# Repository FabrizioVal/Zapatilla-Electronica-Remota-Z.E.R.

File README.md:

# Este proyecto se a redirigido [aquí!](https://github.com/RodrigoSturm14/Zapatilla-Electronica-Remota-Z.E.R-)

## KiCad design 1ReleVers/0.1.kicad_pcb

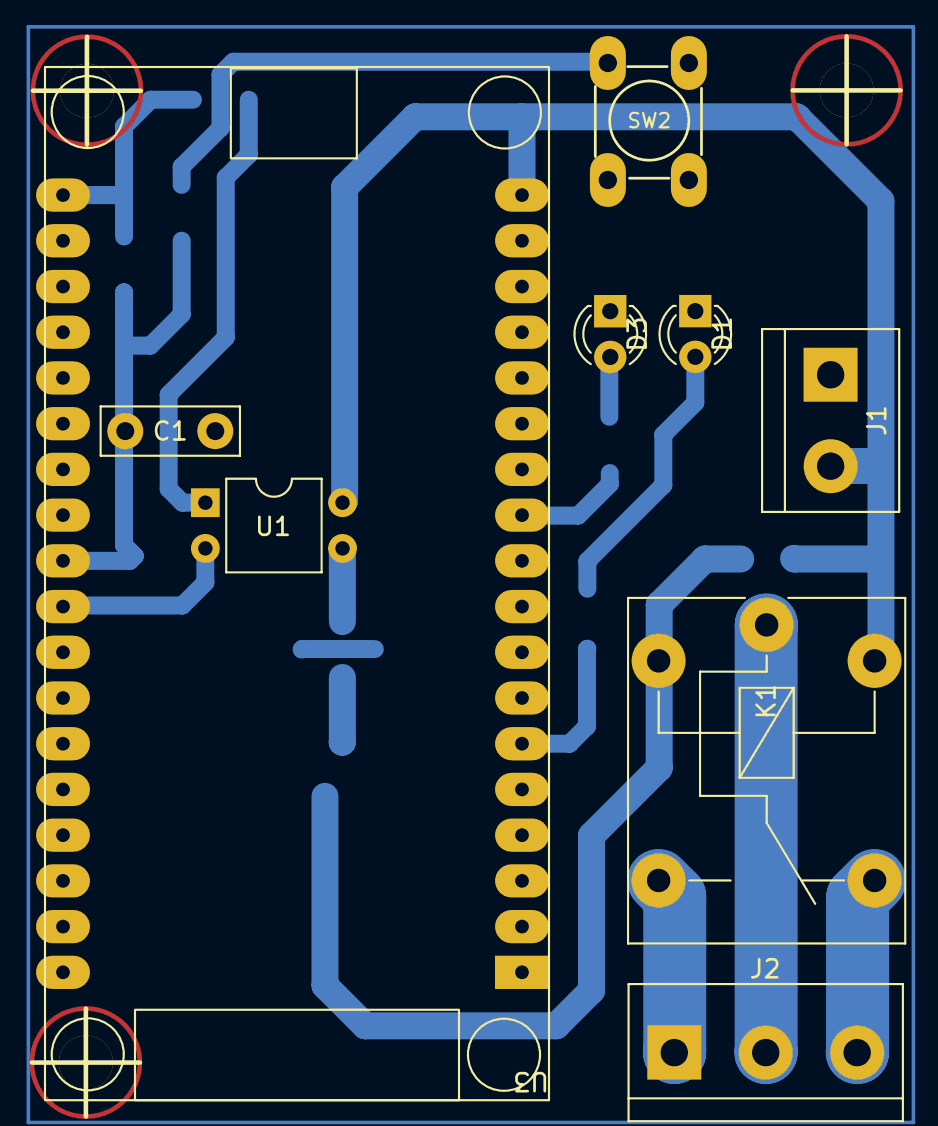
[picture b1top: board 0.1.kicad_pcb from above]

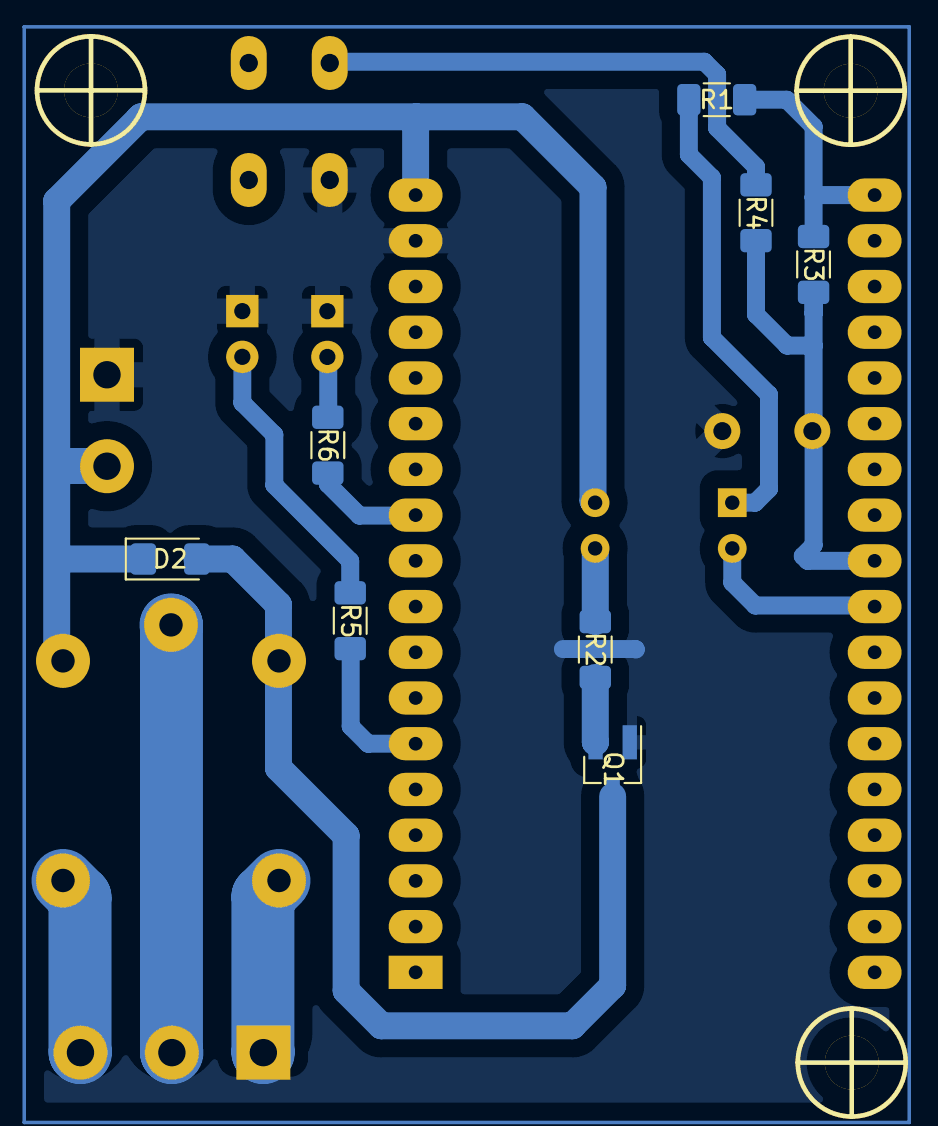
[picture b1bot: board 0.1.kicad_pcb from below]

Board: 2 copper layers, 20 parts (8 on the bottom side), 17 nets.

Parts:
C1: C; C_Disc_D7.5mm_W2.5mm_P5.00mm
D1, D3: LED; LED_D3.0mm
D2: D_Shockley; D_1206_3216Metric_Pad1.42x1.75mm_HandSolder
J1: Entrada 5v; TerminalBlock_bornier-2_P5.08mm
J2: Relay1; TerminalBlock_bornier-3_P5.08mm
K1: G5V-1; Relay_SPDT_Finder_36.11
Q1: S8050; SOT-23_Handsoldering
R1, R2: 1k; R_1206_3216Metric_Pad1.30x1.75mm_HandSolder
R3: 4,7k; R_1206_3216Metric_Pad1.30x1.75mm_HandSolder
R4, R5, R6: R; R_1206_3216Metric_Pad1.30x1.75mm_HandSolder
SW2: SW_Push; PUSH_SWITCH_THT
U1: PC817; DIP-4_W7.62mm
U3: ESP32_DevKit_V1_DOIT; ESP32_Devkit_V1_36pin
hole_3mm, hole_3mm#2, hole_3mm#3: VAL**; hole_3mm

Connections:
+3V3: R1.1, R3.1, U3.19 (3V3)
+5V: D2.1 (K), J1.2, K1.2, U1.4, U3.18 (VIN)
/BT_Config: C1.1, R3.2, R4.2, U3.27 (RX2)
/COM1: J2.2, K1.5
/IN1: U1.2, U3.28 (TX2)
/LED_ConfigBT: R5.1, U3.6 (IO32)
/LED_ConfigWIFI: R6.1, U3.11 (IO14)
/NC1: J2.3, K1.1
/NO1: J2.1, K1.10
GND: C1.2, D1.1 (K), D3.1 (K), J1.1, Q1.1 (E), SW2.2, U3.17 (GND)
unnamed: D1.2 (A), R5.2
unnamed: D2.2 (A), K1.9, Q1.3 (C)
unnamed: D3.2 (A), R6.2
unnamed: Q1.2 (B), R2.2
unnamed: R1.2, U1.1
unnamed: R2.1, U1.3
unnamed: R4.1, SW2.1

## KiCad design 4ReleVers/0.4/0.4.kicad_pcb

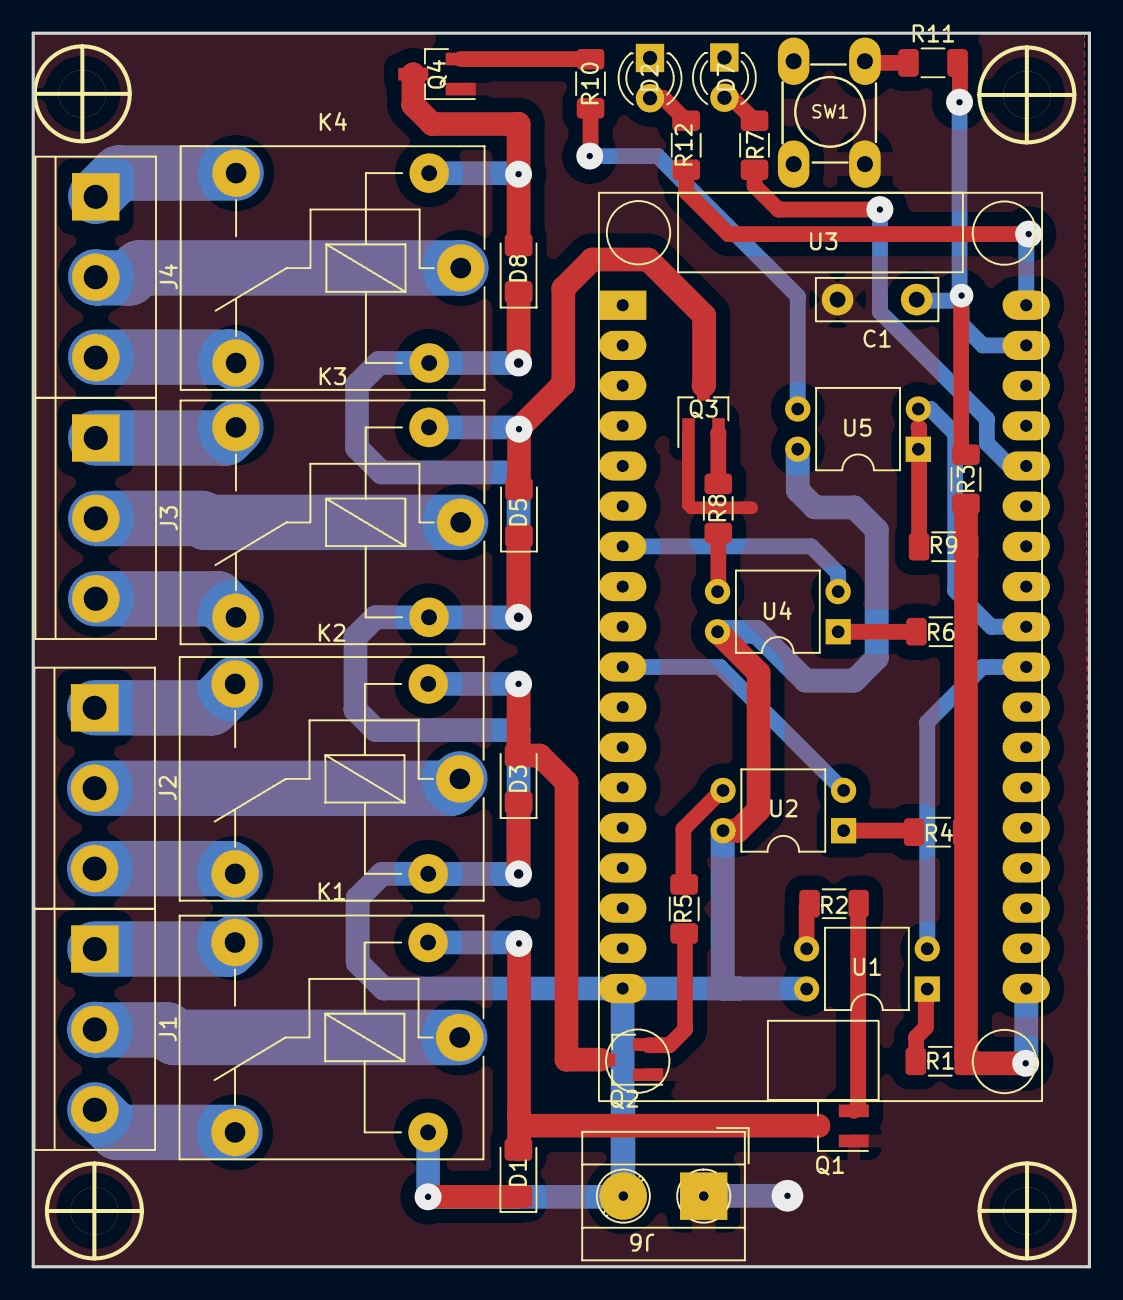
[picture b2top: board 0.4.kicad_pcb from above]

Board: 2 copper layers, 66.7 x 78.0 mm, 42 parts (0 on the bottom side), 41 nets.

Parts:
C1: C; C_Disc_D7.5mm_W2.5mm_P5.00mm
D1, D3, D5, D8: D_Shockley; D_1206_3216Metric_Pad1.42x1.75mm_HandSolder
D2, D7: LED; LED_D3.0mm
J1: Relay1; TerminalBlock_bornier-3_P5.08mm
J2: Relay2; TerminalBlock_bornier-3_P5.08mm
J3: Relay3; TerminalBlock_bornier-3_P5.08mm
J4: Relay4; TerminalBlock_bornier-3_P5.08mm
J6: Entrada 5V; TerminalBlock_1x02_P5.08mm_Horizontal_Personal
K1, K2, K3, K4: G5V-1; Relay_SPDT_Finder_36.11
Q1, Q2, Q3, Q4: S8050; SOT-23_Handsoldering
R1, R2, R4, R5, R6, R8, R9, R10: 1k; R_1206_3216Metric_Pad1.30x1.75mm_HandSolder
R3: 4,7k; R_1206_3216Metric_Pad1.30x1.75mm_HandSolder
R7, R11, R12: R; R_1206_3216Metric_Pad1.30x1.75mm_HandSolder
SW1: SW_Push; PUSH_SWITCH_THT
U1, U2, U4, U5: PC817; DIP-4_W7.62mm
U3: ESP32_DevKit_V1_DOIT; ESP32_Devkit_V1_36pin
hole_3mm, hole_3mm#2, hole_3mm#3, hole_3mm#4: VAL**; hole_3mm

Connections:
+3V3: R1.1, R3.1, R4.1, R6.1, R9.1, U3.19 (3V3)
+5V: D1.1 (K), D3.1 (K), D5.1 (K), D8.1 (K), J6.2, K1.2, K2.2, K3.2, K4.2, U1.4, U2.4, U3.18 (VIN), U4.4, U5.4
/BT_Config: C1.1, R3.2, R11.2, U3.35 (IO22)
/COM1: J1.2, K1.5
/COM2: J2.2, K2.5
/COM3: J3.2, K3.5
/COM4: J4.2, K4.5
/IN1: U1.2, U3.27 (RX2)
/IN2: U2.2, U3.10 (IO27)
/IN3: U3.7 (IO33), U4.2
/IN4: U3.28 (TX2), U5.2
/LED_ConfigBT: R12.1, U3.36 (IO23)
/LED_ConfigWIFI: R7.1, U3.32 (IO21)
/NC1: J1.3, K1.1
/NC2: J2.3, K2.1
/NC3: J3.3, K3.1
/NC4: J4.3, K4.1
/NO1: J1.1, K1.10
/NO2: J2.1, K2.10
/NO3: J3.1, K3.10
/NO4: J4.1, K4.10
GND: C1.2, D2.1 (K), D7.1 (K), J6.1, Q1.1 (E), Q2.1 (E), Q3.1 (E), Q4.1 (E), SW1.2, U3.17 (GND)
unnamed: D1.2 (A), K1.9, Q1.3 (C)
unnamed: D2.2 (A), R12.2
unnamed: D3.2 (A), K2.9, Q2.3 (C)
unnamed: D5.2 (A), K3.9, Q3.3 (C)
unnamed: D7.2 (A), R7.2
unnamed: D8.2 (A), K4.9, Q4.3 (C)
unnamed: Q1.2 (B), R2.2
unnamed: Q2.2 (B), R5.2
unnamed: Q3.2 (B), R8.2
unnamed: Q4.2 (B), R10.2
unnamed: R1.2, U1.1
unnamed: R2.1, U1.3
unnamed: R4.2, U2.1
unnamed: R5.1, U2.3
unnamed: R6.2, U4.1
unnamed: R8.1, U4.3
unnamed: R9.2, U5.1
unnamed: R10.1, U5.3
unnamed: R11.1, SW1.1

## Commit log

2023-05-10 Se han añadido 5 archivos principales nuevos
2023-05-10 main activity kt actualizada
2023-05-24 Primer version
2023-05-24 comienzo de la integracion de botones para subscribe
2023-05-29 segui trabajando en subscribe, ver datastore y clases extras
2023-05-31 Segui trabajando en subscribe. Necesitamos relacionar "text" con topic, para poder ingresar el nombre del topic en el edittext
2023-05-31 Trabaje en subscribe, necesitamos relacionar variable text con topic para poder ingresar un nombre en edittext y que se subscriba a este
2023-06-09 added a LICENSE
